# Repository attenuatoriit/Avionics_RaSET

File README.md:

# Avionics_RaSET
This repository encompasses all the updates regarding the rocket avionics (MaxQ) that has beendeveloped in house by the IIT Kanpur Rocketry and Space Exploration Team. The avionics has been designed keeping in mind Space Port America Cup 10k SRAD category. There are mainly three main components of the avionics - flight computer, arming switch and telemetry.  The flight computer encompasses the ltimeter, IMU, micro controller and GPS. It also has ports to support to different telemetry devices- Xbee and LoRA. The use of a micro processor is being planned on the flight computer in ot=rder to facilitate the implementation of trajectory plnning of the rocket during its flight.

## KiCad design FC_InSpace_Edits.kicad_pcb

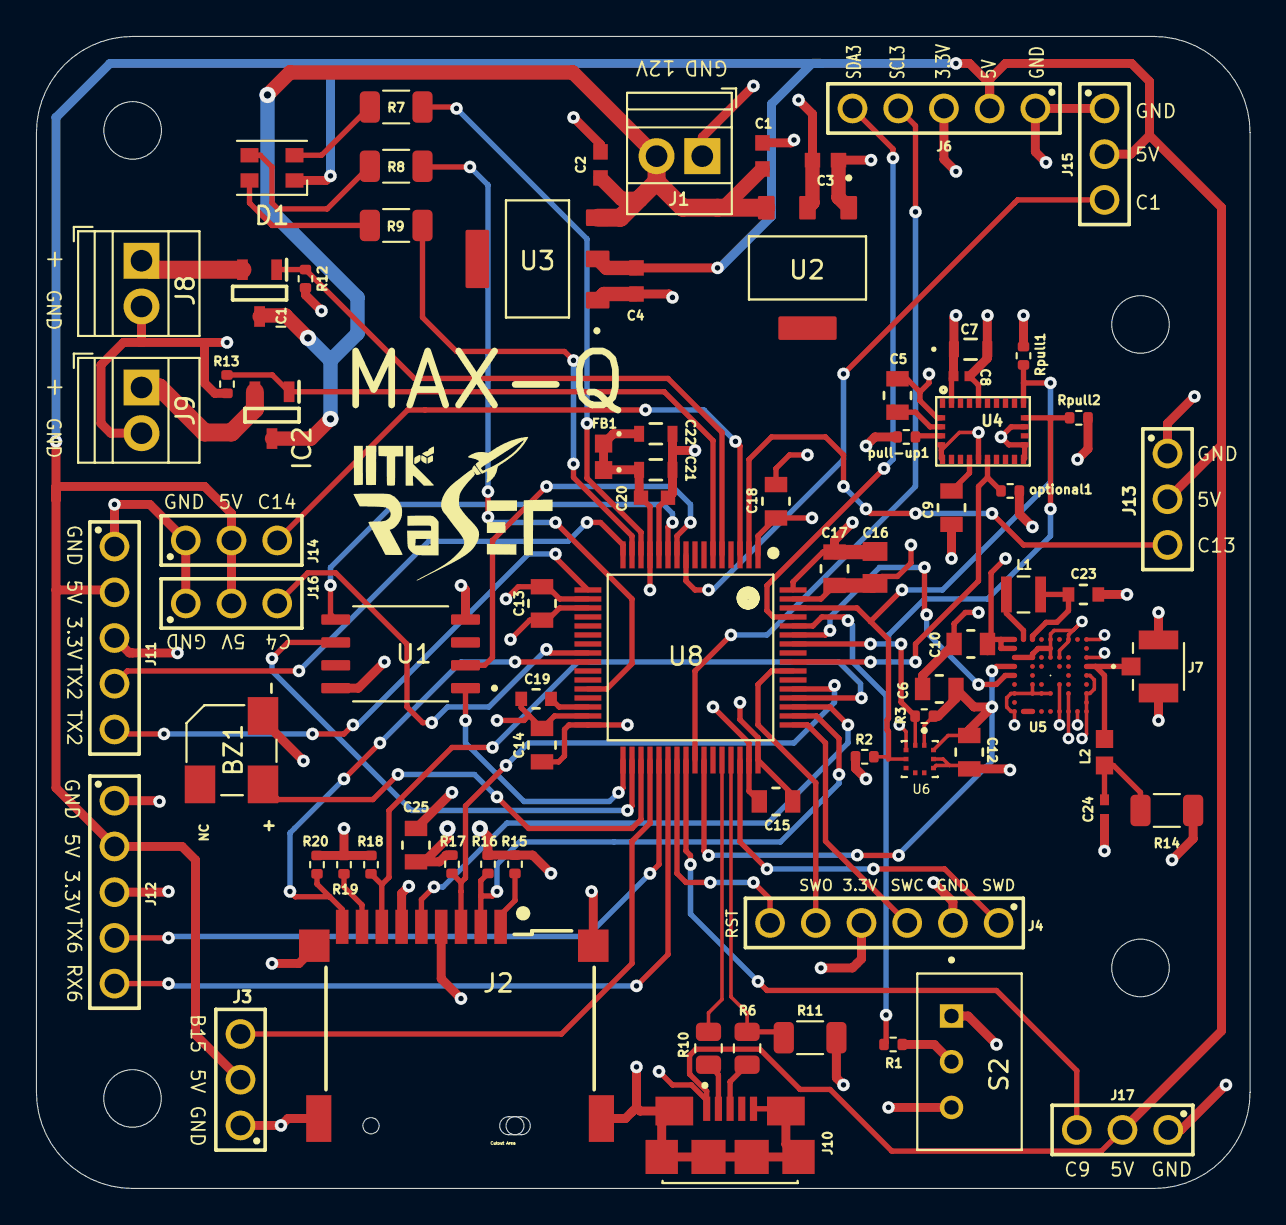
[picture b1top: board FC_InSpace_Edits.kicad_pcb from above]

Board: 4 copper layers, 67.4 x 64.0 mm, 77 parts (0 on the bottom side), 62 nets.

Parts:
BZ1: Buzzer; CUI_CSS-0575B-SMT
C1, C2, C3, C4: 22u; G-188_MUR
C5, C6, C9, C12: 100nF; CAP_CL21_SAM
C7: 6.8nF; CAP_1608_TDK
C8: 120nF; CAP_CC0402_YAG
C10: 0.1 uF; CAP_CL21_SAM
C13, C14, C15, C17, C18, C25: 100n; CAP_CL21_SAM
C16: 10u; CAPC2012X135N
C19: 4.7u; CAP_CL10_SAM
C20: 10n; WCAP-CSMH_0603_R
C21, C22: 1u; CAP_1608_TDK
C23: 4.7 uF; CAP_CL10_SAM
C24: 47 pF; G-155_MUR
D1: CLV1L-FKB; LED_Cree-PLCC4_3.2x2.8mm_CCW
FB1: 120R; BEADC1608X75N
IC1, IC2: NMOS; SOT95P285X130-3N
J1: Screw_Terminal; TerminalBlock_Xinya_XY308-2.54-2P_1x02_P2.54mm_Horizontal
J2: SD Card FC; 693071020811
J3, J13, J14, J15, J16, J17: Headers 3x1 FC; 61300311121
J4: Headers ST-Link; 61300611121
J6, J11, J12: Headers 5x1 FC; 61300511121
J7: U.FL-R-SMT_10_; HRS_U.FL-R-SMT_10_
J8, J9: Screw_Terminal_01x02; TerminalBlock_Xinya_XY308-2.54-2P_1x02_P2.54mm_Horizontal
J10: MicroUSB FC; AMPHENOL_10118192-0002LF
L1: 2.2 uH; IND_VLS252012HBX-2R2M-1
L2: L_Ferrite; BEADC1608X75N
R1, R15, R16, R17, R18, R19, R20: 10k; R_0402_1005Metric
R2, R3: 4.7k; R_0402_1005Metric
R6, R10: 20; R_0805_2012Metric
R7: 150; R_1206_3216Metric
R8, R9: 130; R_1206_3216Metric
R11: 1.5k; R_1206_3216Metric
R12, R13: 10K; R_0402_1005Metric
R14: 10; R_1206_3216Metric
Rpull1, Rpull2: 10k; R_0402_1005Metric
S2: Switch2 FC; SW_MPB01-1C33-S-D
U1: W25Q128JVS; SOIC127P790X216-8N
U2: AMS1117-3.3; SOT229P700X180-4N
U3: AMS1117-5.0; SOT229P700X180-4N
U4: BNO055; LGA28R50P4X10_380X520X100
U5: ZOE-M8Q; ZOE-M8
U6: BMP390L; XDCR_BMP390L
U8: STM32F411RETx; QFP50P1200X1200X160-64N
optional1: 10k; R_0402_1005Metric
pull-up1: 10k; R_0402_1005Metric

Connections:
+3.3V: C3.1, C6.2, C7.1, C8.1, C10.1, C12.2, C13.1, C14.1, C15.1, C16.1, C17.1, C18.1, C20.1, C21.1, C22.1, C25.1, FB1.1, FB1.2, J2.4 (VDD), J4.4, J6.3, J11.3, J12.3, R2.1, R3.2, R11.2, R14.1, R15.1, R16.1, R17.1, R18.1, R19.1, R20.1, Rpull1.1, Rpull2.1, S2.1, U1.8 (VCC), U2.2 (VO), U4.28 (VDDIO), U5.P$J1 (J1_VCC), U5.P$J2 (J2_VCC), U6.1 (VDDIO), U6.10 (VDD), U8.1 (VBAT), U8.13 (VDDA), U8.19 (VDD), U8.32 (VDD), U8.48 (VDD), U8.64 (VDD), optional1.1, pull-up1.1
+5V: C4.1, D1.1 (A), J3.2, J6.2, J10.1 (VCC), J11.2, J12.2, J13.2, J14.2, J15.2, J16.2, J17.2, U3.2 (VO)
/BOOT0: R1.1, U8.60 (BOOT0)
/BUZZER: BZ1.1, U8.35 (PB14)
/D+: R6.2, R11.1, U8.45 (PA12)
/D-: R10.2, U8.44 (PA11)
/FLASHMEM_CS: U1.1 (~CS), U8.33 (PB12)
/FLASHMEM_MISO: U1.2 (DO(IO1)), U8.10 (PC2)
/FLASHMEM_MOSI: U1.5 (DI(IO0)), U8.11 (PC3)
/FLASHMEM_SCLK: U1.6 (CLK), U8.34 (PB13)
/H1: J3.3, U8.36 (PB15)
/H2: J13.3, U8.2 (PC13)
/H3: J14.3, U8.3 (PC14)
/H4: J15.3, U8.9 (PC1)
/H5: J16.3, U8.24 (PC4)
/H7: J17.3, U8.40 (PC9)
/I2C3_SCL: J6.4, U8.41 (PA8)
/I2C3_SDA: J6.5, U8.61 (PB8)
/IMU_RESET: U4.11 (~RESET), U8.56 (PB4), optional1.2
/L1_BLU: R9.1, U8.15 (PA1)
/L1_GRE: R8.1, U8.28 (PB2)
/L1_RED: R7.1, U8.14 (PA0)
/PYRO_1: IC1.1 (G), R12.1, U8.5 (PH0)
/PYRO_2: IC2.1 (G), R13.1, U8.6 (PH1)
/SD_CS: J2.2 (CD/DAT3), R16.2, U8.50 (PA15)
/SD_DET: J2.9 (CDSW1), R20.2, U8.25 (PC5)
/SD_MISO: J2.7 (DAT0), R18.2, U8.52 (PC11)
/SD_MOSI: J2.3 (CMD), R17.2, U8.53 (PC12)
/SD_SCLK: J2.5 (CLK), U8.51 (PC10)
/USART1_RX: U5.P$J5 (J5_TXD/SPI_MISO), U8.59 (PB7)
/USART1_TX: U5.P$J4 (J4_RXD/SPI_MOSI), U8.42 (PA9)
/USART2_RX: J11.5, U8.17 (PA3)
/USART2_TX: J11.4, U8.16 (PA2)
/USART6_RX: J12.5, U8.38 (PC7)
/USART6_TX: J12.4, U8.37 (PC6)
GND: BZ1.2, C1.2, C2.2, C3.2, C4.2, C5.2, C6.1, C7.2, C8.2, C9.1, C10.2, C12.1, C13.2, C14.2, C15.2, C16.2, C17.2, C18.2, C19.1, C20.2, C21.2, C22.2, C23.1, C24.2, C25.2, J1.1, J2.6 (VSS), J2.10 (GND), J2.11 (GND), J2.12 (GND), J2.13 (GND), J3.1, J4.2, J6.1, J7.2, J7.3, J8.2, J9.2, J10.5 (GND), J10.S1 (SHIELD), J10.S2 (SHIELD), J10.S3 (SHIELD), J10.S4 (SHIELD), J10.S5 (SHIELD), J10.S6 (SHIELD), J11.1, J12.1, J13.1, J14.1, J15.1, J16.1, J17.1, R12.2, R13.2, S2.3, U1.4 (GND), U2.1 (GND), U3.1 (GND), U4.2 (GND), U4.5 (PS1), U4.6 (PS0), U4.10 (BL_IND), U4.15 (GNDIO), U4.16 (GNDIO), U4.18 (COM2), U4.25 (GNDIO), U5.P$2E1 (E1_SQI_CLK), U5.P$A1 (A1_GND), U5.P$A3 (A3_GND), U5.P$A5 (A5_GND), U5.P$A7 (A7_GND), U5.P$A8 (A8_GND), U5.P$A9 (A9_GND), U5.P$B9 (B9_GND), U5.P$C1 (C1_SQI_D1), U5.P$C7 (C7_GND), U5.P$C9 (C9_GND), U5.P$D3 (D3_SQI_CS_N), U5.P$D6 (D6_GND), U5.P$D9 (D9_GND), U5.P$E3 (E3_SQI_D2), U5.P$E7 (E7_GND), U5.P$F7 (F7_GND), U5.P$G3 (G3_GND), U5.P$G6 (G6_GND), U5.P$G7 (G7_GND), U5.P$J3 (J3_GND), U5.P$J7 (J7_RTC_I), U5.P$J9 (J9_GND), U6.3 (VSS/GND), U6.8 (VSS/GND), U6.9 (VSS/GND), U8.12 (VSSA), U8.18 (VSS), U8.31 (VSS), U8.47 (VSS), U8.63 (VSS)
unnamed: C24.1, L2.1, R14.2
unnamed: D1.4 (BK), R9.2
unnamed: D1.3 (GK), R8.2
unnamed: D1.2 (RK), R7.2
unnamed: IC1.2 (S), J8.1
unnamed: IC2.2 (S), J9.1
unnamed: J2.8 (DAT1), R19.2
unnamed: J2.1 (DAT2), R15.2
unnamed: J10.3 (D+), R6.1
unnamed: J10.2 (D-), R10.1
unnamed: R1.2, S2.2
unnamed: C9.2, U4.9 (CAP)
unnamed: C5.1, U4.3 (VDD)
unnamed: U4.4 (~BOOT_LOAD_PIN), pull-up1.2
unnamed: J7.1, L2.2, U5.P$A4 (A4_RF_IN)
unnamed: U5.P$G9 (G9_RESERVED), U5.P$H9 (H9_V_BCKP)
unnamed: C23.2, L1.1, U5.P$G1 (V_CORE)
unnamed: L1.2, U5.P$H1 (V_DCDC_OUT)
unnamed: C19.2, U8.30 (VCAP1)
RST: J4.6, U8.39 (PC8)
SCL1: R3.1, Rpull2.2, U4.19 (COM1), U6.2 (SCK/SCL), U8.58 (PB6)
SDA1: R2.2, Rpull1.2, U4.20 (COM0), U6.4 (SDI/SDO/SDA), U8.62 (PB9)
SWCLK: J4.3, U8.49 (PA14)
SWDIO: J4.1, U8.46 (PA13)
SWO: J4.5, U8.55 (PB3)
VDB: C1.1, C2.1, IC1.3 (D), IC2.3 (D), J1.2, U2.3 (VI), U3.3 (VI)

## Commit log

2024-10-18 Update_1 README.md
2026-03-22 PCB files committed
